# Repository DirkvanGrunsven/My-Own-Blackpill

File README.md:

# My Own Blackpill
 My first attempt at creating a PCB with an STM32 MCU

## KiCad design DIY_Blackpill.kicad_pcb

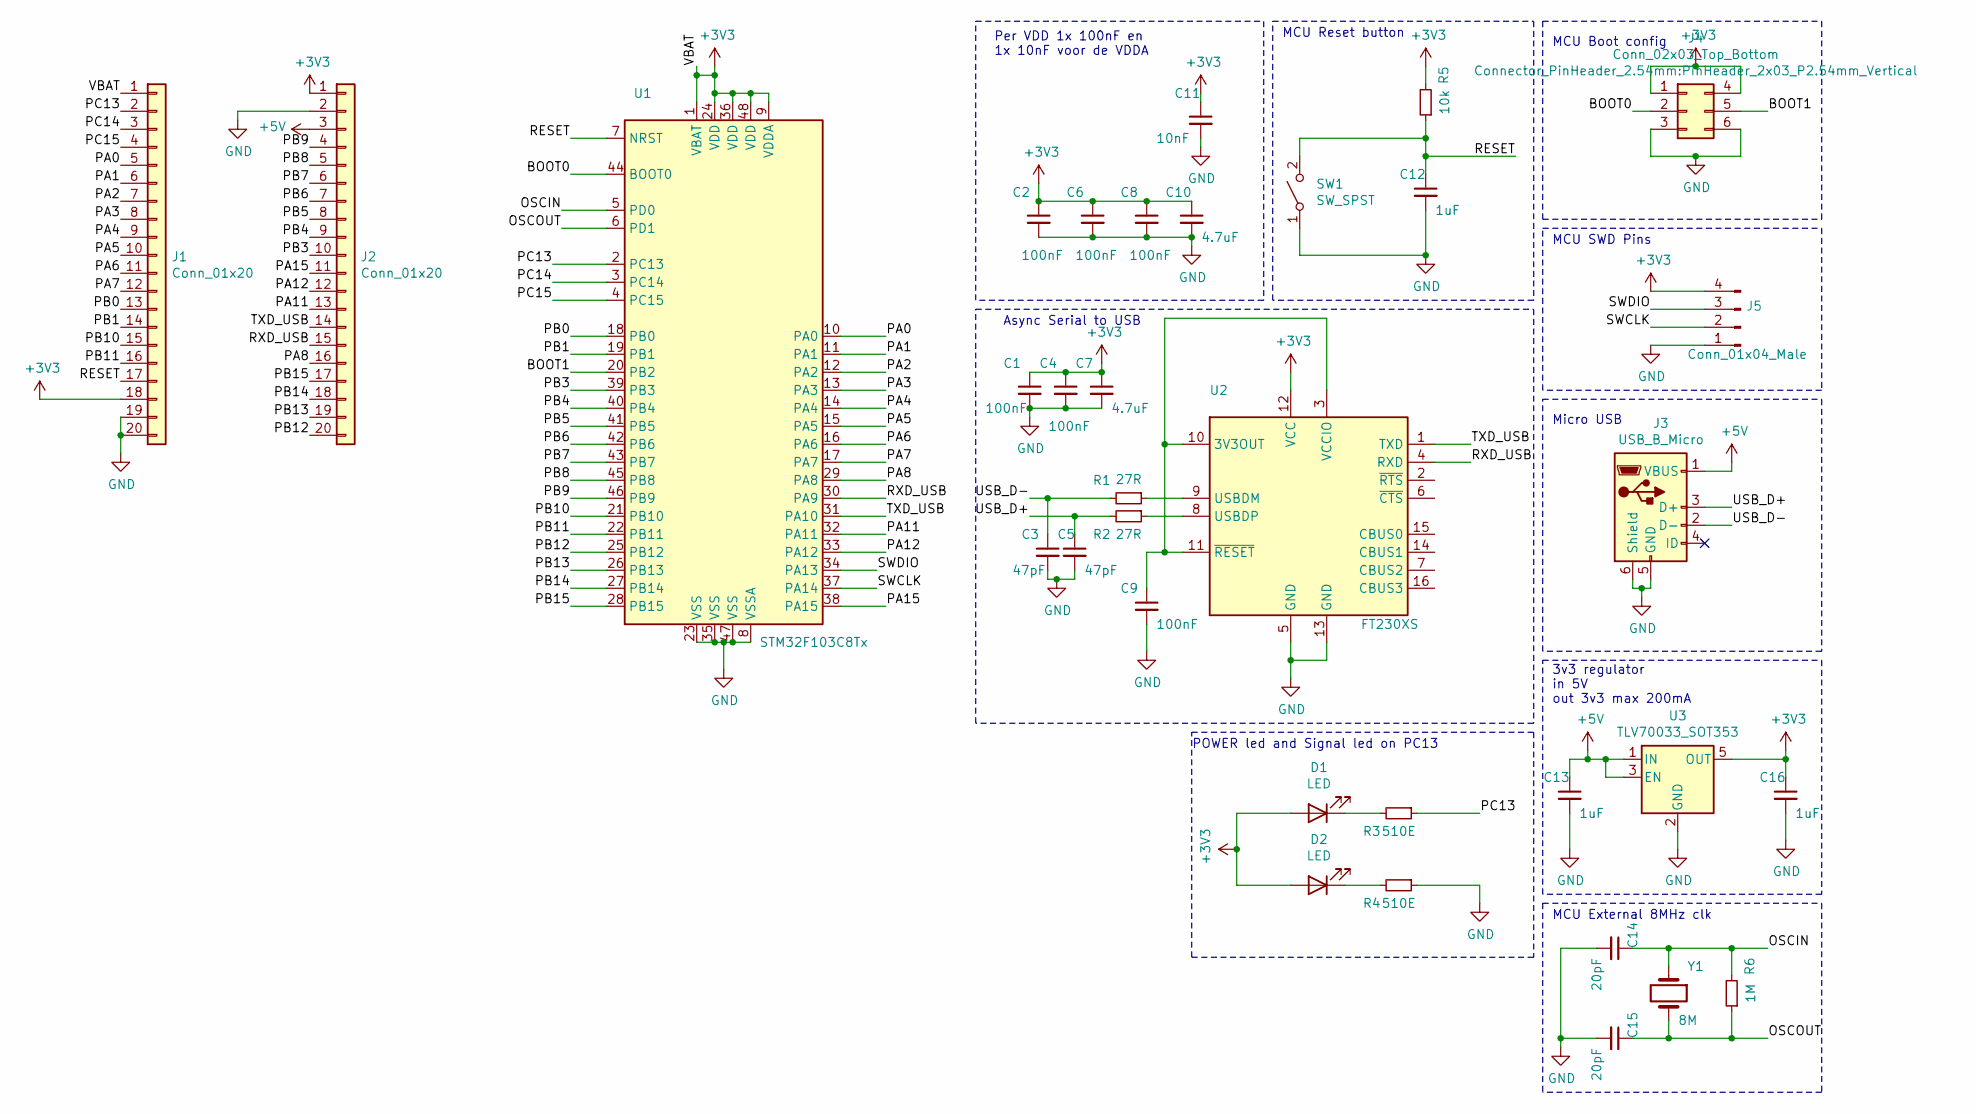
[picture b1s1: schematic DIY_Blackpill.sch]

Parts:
C1, C2, C4, C6, C8, C9: 100nF; C_0805_2012Metric_Pad1.15x1.40mm_HandSolder
C3, C5: 47pF; C_0805_2012Metric_Pad1.15x1.40mm_HandSolder
C7, C10: 4.7uF; C_0805_2012Metric_Pad1.15x1.40mm_HandSolder
C11: 10nF; C_0805_2012Metric_Pad1.15x1.40mm_HandSolder
C12, C13, C16: 1uF; C_0805_2012Metric_Pad1.15x1.40mm_HandSolder
C14, C15: 20pF; C_0805_2012Metric_Pad1.15x1.40mm_HandSolder
D1, D2: LED; LED_0805_2012Metric_Pad1.15x1.40mm_HandSolder
J1, J2: Conn_01x20; PinHeader_1x20_P2.54mm_Vertical
J3: USB_B_Micro; USB_Micro-B_Wuerth_629105150521
J4: Conn_02x03_Top_Bottom; PinHeader_2x03_P2.54mm_Vertical
J5: Conn_01x04_Male; PinHeader_1x04_P2.54mm_Vertical
R1, R2: 27R; R_0805_2012Metric_Pad1.15x1.40mm_HandSolder
R3, R4: 510E; R_0805_2012Metric_Pad1.15x1.40mm_HandSolder
R5: 10k; R_0805_2012Metric_Pad1.15x1.40mm_HandSolder
R6: 1M; R_0805_2012Metric_Pad1.15x1.40mm_HandSolder
SW1: SW_SPST; RS282G05A3SMRT
U1: STM32F103C8Tx; LQFP-48_7x7mm_P0.5mm
U2: FT230XS; SSOP-16_3.9x4.9mm_P0.635mm
U3: TLV70033_SOT353; SOT95P280X110-5N
Y1: 8M; Crystal_HC49-U_Vertical

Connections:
+3V3: C1.1, C2.1, C4.1, C6.1, C7.1, C8.1, C10.1, C11.1, C16.1, D1.2 (A), D2.2 (A), J1.1, J1.18, J2.1, J4.1, J4.4, J5.4, R5.2, U1.1 (VBAT), U1.9 (VDDA), U1.24 (VDD), U1.36 (VDD), U1.48 (VDD), U2.12 (VCC), U3.5 (OUT)
+5V: C13.1, J2.3, J3.1 (VBUS), U3.1 (IN), U3.3 (EN)
/BOOT0: J4.2, U1.44 (BOOT0)
/BOOT1: J4.5, U1.20 (PB2)
/OSCIN: C14.1, R6.2, U1.5 (PD0), Y1.1
/OSCOUT: C15.1, R6.1, U1.6 (PD1), Y1.2
/PA0: J1.5, U1.10 (PA0)
/PA1: J1.6, U1.11 (PA1)
/PA2: J1.7, U1.12 (PA2)
/PA3: J1.8, U1.13 (PA3)
/PA4: J1.9, U1.14 (PA4)
/PA5: J1.10, U1.15 (PA5)
/PA6: J1.11, U1.16 (PA6)
/PA7: J1.12, U1.17 (PA7)
/PA8: J2.16, U1.29 (PA8)
/PA11: J2.13, U1.32 (PA11)
/PA12: J2.12, U1.33 (PA12)
/PA15: J2.11, U1.38 (PA15)
/PB0: J1.13, U1.18 (PB0)
/PB1: J1.14, U1.19 (PB1)
/PB3: J2.10, U1.39 (PB3)
/PB4: J2.9, U1.40 (PB4)
/PB5: J2.8, U1.41 (PB5)
/PB6: J2.7, U1.42 (PB6)
/PB7: J2.6, U1.43 (PB7)
/PB8: J2.5, U1.45 (PB8)
/PB9: J2.4, U1.46 (PB9)
/PB10: J1.15, U1.21 (PB10)
/PB11: J1.16, U1.22 (PB11)
/PB12: J2.20, U1.25 (PB12)
/PB13: J2.19, U1.26 (PB13)
/PB14: J2.18, U1.27 (PB14)
/PB15: J2.17, U1.28 (PB15)
/PC13: J1.2, R3.1, U1.2 (PC13)
/PC14: J1.3, U1.3 (PC14)
/PC15: J1.4, U1.4 (PC15)
/RESET: C12.1, J1.17, R5.1, SW1.2 (B), U1.7 (NRST)
/RXD_USB: J2.15, U1.30 (PA9), U2.4 (RXD)
/SWCLK: J5.2, U1.37 (PA14)
/SWDIO: J5.3, U1.34 (PA13)
/TXD_USB: J2.14, U1.31 (PA10), U2.1 (TXD)
/USB_D+: C5.1, J3.3 (D+), R2.2
/USB_D-: C3.1, J3.2 (D-), R1.2
GND: C1.2, C2.2, C3.2, C4.2, C5.2, C6.2, C7.2, C8.2, C9.2, C10.2, C11.2, C12.2, C13.2, C14.2, C15.2, C16.2, J1.19, J1.20, J2.2, J3.5 (GND), J3.6 (Shield), J4.3, J4.6, J5.1, R4.1, SW1.1 (A), U1.8 (VSSA), U1.23 (VSS), U1.35 (VSS), U1.47 (VSS), U2.5 (GND), U2.13 (GND), U3.2 (GND)
unnamed: C9.1, U2.3 (VCCIO), U2.10 (3V3OUT), U2.11 (~RESET)
unnamed: D1.1 (K), R3.2
unnamed: D2.1 (K), R4.2
unnamed: R1.1, U2.9 (USBDM)
unnamed: R2.1, U2.8 (USBDP)

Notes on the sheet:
MCU Boot config
MCU SWD Pins
Micro USB
3v3 regulator in 5V out 3v3 max 200mA
MCU Reset button
Async Serial to USB
MCU External 8MHz clk
Per VDD 1x 100nF en 1x 10nF voor de VDDA
POWER led and Signal led on PC13

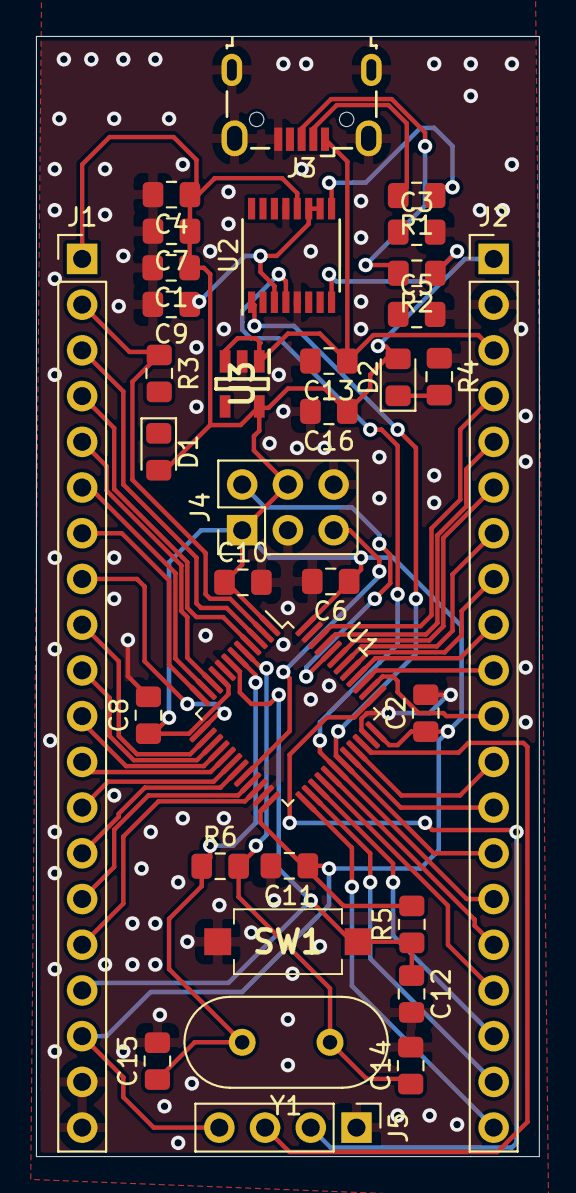
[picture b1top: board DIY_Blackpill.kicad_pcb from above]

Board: 2 copper layers, 27.9 x 62.2 mm, 34 parts (0 on the bottom side), 49 nets.

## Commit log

2021-02-05 Add all the KiCad files from V1
2021-02-05 Switched Footprint of TVL70033
2021-02-05 Added way more via's
2021-02-05 made new gbt files
2021-02-07 made jlcpcb zipfolder
